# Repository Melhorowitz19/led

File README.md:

# Usage Notes

Pressing the button on the top of the device changes the state of the LED.
- 0: OFF
- 1: BRIGHT
- 2: INTERMEDIATE
- 3: DIM
- 4: 2 HZ FLASHING

In order to conserve battery, the battery is unattached while the device is not in use. In order to turn ON, remove the lid, attach the 9 V battery to the clip, and place flat in the empty compartment.

### ECAD Changes

While testing, some changes had to be made to the PCB post-photoetching. In particular, R2 and R4 were removed, and the button was attached directly to pin 4 of the ATMega, bypassing the Zener diode. These two resistors caused voltage division that caused the microcontroller to not register the button pressing.

### Lid/CAD Notes

The lid does not fit entirely within the box, but the fit is tight enough that it remains despite not being perfect. This lid was chosen for the final product in order to minimize the risk of collisions between the PCB components in the lid while keeping a tight fit for the battery. In order to add extra security, tape can be added to the lid (though it is not needed). A future iteration of the lid was created in SolidWorks (which can be seen in the Mechanical directory) that allows more space and a tighter fit if desired.

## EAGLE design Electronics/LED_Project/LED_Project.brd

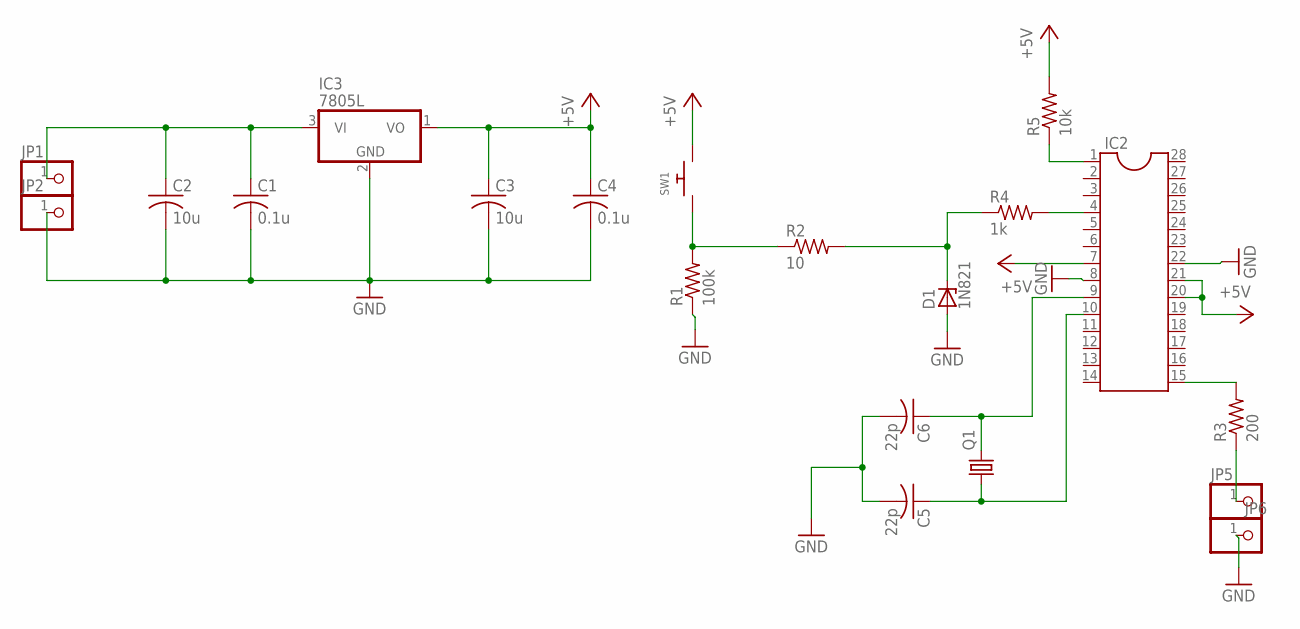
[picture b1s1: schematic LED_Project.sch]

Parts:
C1, C4: 0.1u; C0805K
C2, C3: 10u; C0805K
C5, C6: 22p; C0805K
D1: 1N821; DO35Z10
IC2: DIL28-3
IC3: 7805L; TO92
JP1, JP2, JP5, JP6: PINHD-1X1; 1X01
Q1: CRYSTALHC49S; HC49/S
R1: 100k; R0805
R2: 10; R0805
R3: 200; R0805
R4: 1k; R0805
R5: 10k; R0805
SW1: SWITCH_PUSHBUTTONSOFTTOUCHSMD_SJ; PUSHBUTTON_SMD_SJ

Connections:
+5V: C3.1, C4.1, IC2.7, IC2.20, IC2.21, IC3.1 (VO), R5.2, SW1.P$2
GND: C1.2, C2.2, C3.2, C4.2, C5.2, C6.2, D1.A, IC2.8, IC2.22, IC3.2 (GND), JP2.1, JP6.1, R1.1
unnamed: C1.1, C2.1, IC3.3 (VI), JP1.1
unnamed: R1.2, R2.1, SW1.P$1
unnamed: IC2.4, R4.2
unnamed: C6.1, IC2.9, Q1.2
unnamed: D1.C, R2.2, R4.1
unnamed: IC2.15, R3.2
unnamed: JP5.1, R3.1
unnamed: C5.1, IC2.10, Q1.1
unnamed: IC2.1, R5.1

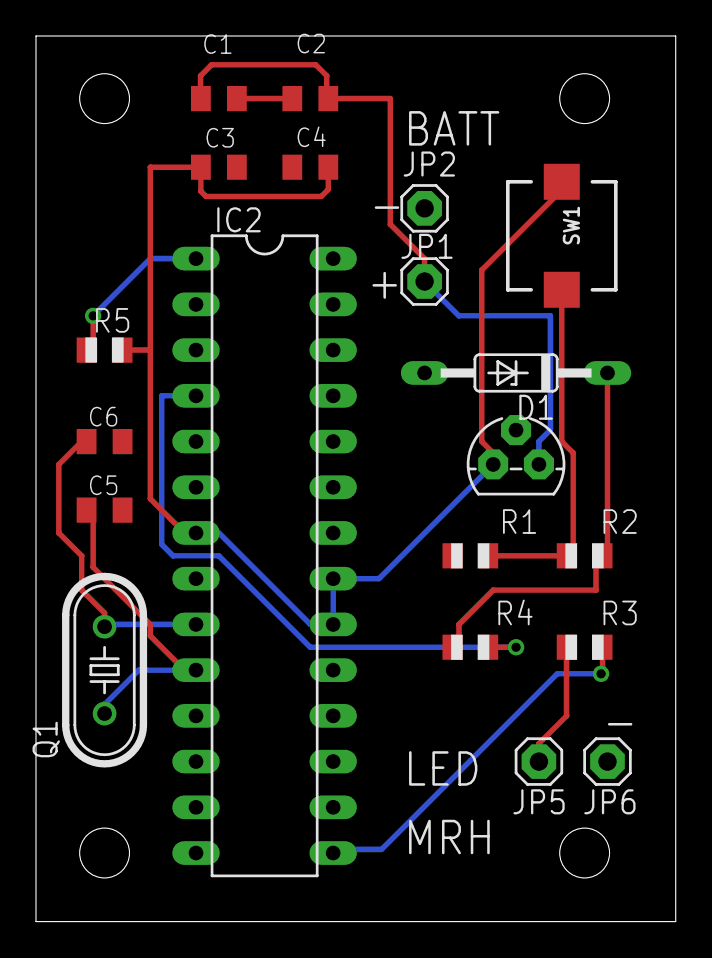
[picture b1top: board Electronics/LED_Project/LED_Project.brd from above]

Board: 2 copper layers, 35.5 x 49.2 mm, 20 parts (0 on the bottom side), 11 nets.

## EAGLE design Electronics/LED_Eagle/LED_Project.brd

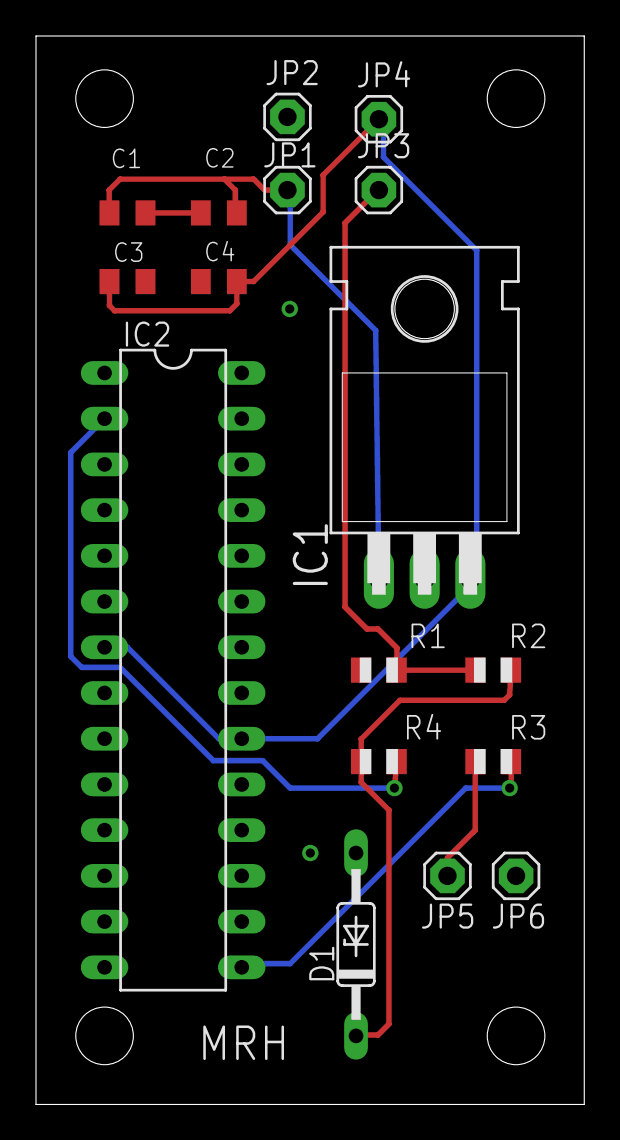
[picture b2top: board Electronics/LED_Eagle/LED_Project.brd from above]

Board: 2 copper layers, 30.5 x 59.4 mm, 17 parts (0 on the bottom side), 8 nets.

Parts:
C1, C4: 0.1u; C0805K
C2, C3: 10u; C0805K
D1: 1N821; DO35Z10
IC1: 7805T; TO220H
IC2: DIL28-3
JP1, JP2, JP3, JP4, JP5, JP6: 1X01
R1: 100k; R0805
R2: 10; R0805
R3: 200; R0805
R4: 1k; R0805

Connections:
+5V: C3.1, C4.1, IC1.3, IC2.7, IC2.20, JP4.1
GND: C1.2, C2.2, C3.2, C4.2, D1.A, IC1.2, IC2.8, IC2.22, JP2.1, JP6.1, R1.1
unnamed: C1.1, C2.1, IC1.1, JP1.1
unnamed: JP3.1, R1.2, R2.1
unnamed: IC2.2, R4.2
unnamed: D1.C, R2.2, R4.1
unnamed: IC2.15, R3.2
unnamed: JP5.1, R3.1

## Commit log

2018-09-26 Added directories
2018-09-29 added functional diagrams for milestone 2
2018-10-28 added first iteration of schematic
2018-10-29 initial software functional block diagram
2018-11-01 updated version of schematic
2018-11-05 led arduino software v1
2018-11-09 all Eagle files for 1st CAD
2018-11-09 first ecad pdfs
2018-11-09 added datasheets
2018-11-17 version 2 of pcb design
2018-11-18 added first version of cad
2018-11-25 3D printed version of CAD
2018-11-26 replacecd ECAD files
2018-11-29 edited code
2018-11-30 video proof of functionality
